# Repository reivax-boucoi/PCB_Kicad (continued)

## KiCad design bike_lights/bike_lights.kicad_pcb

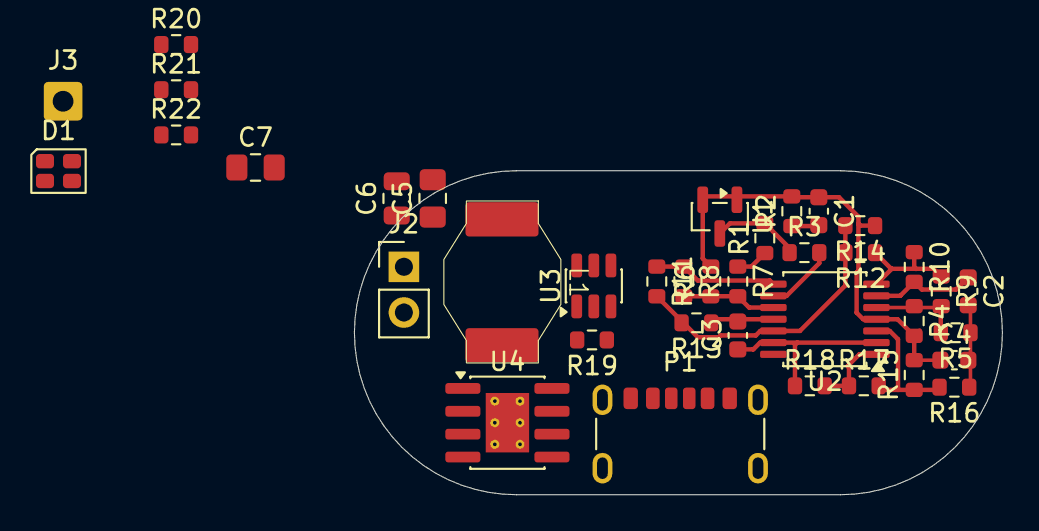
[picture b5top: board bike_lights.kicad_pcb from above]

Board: 2 copper layers, 36.0 x 18.0 mm, 39 parts (1 on the bottom side), 23 nets.

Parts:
C1, C3, C4: 100n; C_0603_1608Metric
C2: 470n; C_0603_1608Metric
C5, C7: 10u; C_0805_2012Metric_Pad1.18x1.45mm_HandSolder
C6: 270n; C_0805_2012Metric
D1: LED_Dual_AAKK; LED_Cree-PLCC4_2x2mm_CW
H1: MountingHole_Pad; SolderWirePad_1x01_SMD_5x10mm
J2: LED; PinHeader_1x02_P2.54mm_Vertical
J3: B+; SolderWire-0.5sqmm_1x01_D0.9mm_OD2.1mm
L1: 10µ; DO1813H
P1: USB_C_Plug_USB2.0; USB_C_Receptacle_GCT_USB4125-xx-x_6P_TopMnt_Horizontal
R1, R20, R21, R22: 1k96; R_0603_1608Metric
R2: 51k; R_0603_1608Metric
R3, R13, R18: 33k; R_0603_1608Metric
R4, R5, R6, R7, R9, R14, R15, R16, R17: 39k; R_0603_1608Metric
R8: 1M; R_0603_1608Metric
R10: 680k; R_0603_1608Metric
R11: 100k; R_0603_1608Metric
R12: 56k; R_0603_1608Metric
R19: 2R2; R_0603_1608Metric
U1: TL431DBZ; SOT-23
U2: MCP6004; TSSOP-14_4.4x5mm_P0.65mm
U3: MIC2289; SOT-23-6
U4: TP4056-42-ESOP8; SOIC-8-1EP_3.9x4.9mm_P1.27mm_EP2.41x3.3mm_ThermalVias

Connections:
+BATT: C1.1, C4.1, C5.1, J3.1, L1.1, R2.2, R4.2, R6.2, R14.1, R15.2, U1.1 (K), U1.2 (REF), U2.4 (V+), U3.5 (Vin), U4.5 (BAT)
/Batt_mon: R6.1, R7.2, R8.2, U2.10 (+)
/Blink: R9.1, R10.1, R12.1, U2.7
/BlinkFB: R4.1, R5.2, R9.2, U2.5 (+)
/BlinkRC: C2.1, R10.2, U2.6 (-)
/EN: U2.14, U3.4 (EN)
/LED+: C6.1, J2.1, U3.6 (OUT)
/LED-: J2.2, R19.1, U3.3 (FB)
/LowBat: R8.1, R11.1, U2.8
/Ramp: C3.1, R18.1, U2.2 (-), U2.13 (-)
/RampFB: R15.1, R16.2, R17.2, U2.3 (+)
/RampOut: R17.1, R18.2, U2.1
/SW: L1.2, U3.1 (SW)
/Sum: R11.2, R12.2, R13.2, R14.2, U2.12 (+)
/Vref: C1.2, R2.1, R3.2, U2.9 (-)
/~CHRG: D1.4 (K2), R20.1
/~STDBY: D1.3 (K1), R21.1
GND: C2.2, C3.2, C4.2, C5.2, C6.2, C7.2, H1.1, P1.A12 (GND), P1.B12 (GND), P1.S1 (SHIELD), R1.1, R5.1, R7.1, R13.1, R16.1, R19.2, R22.1, U2.11 (V-), U3.2 (GND), U4.3 (GND), U4.9 (EPAD)
unnamed: C7.1, D1.1 (A1), D1.2 (A2), P1.A9 (VBUS), P1.B9 (VBUS), U4.4 (V_{CC}), U4.8 (CE)
unnamed: R1.2, R3.1, U1.3 (A)
unnamed: R22.2, U4.2 (PROG)
unnamed: R20.2, U4.7 (~CHRG)
unnamed: R21.2, U4.6 (~STDBY)

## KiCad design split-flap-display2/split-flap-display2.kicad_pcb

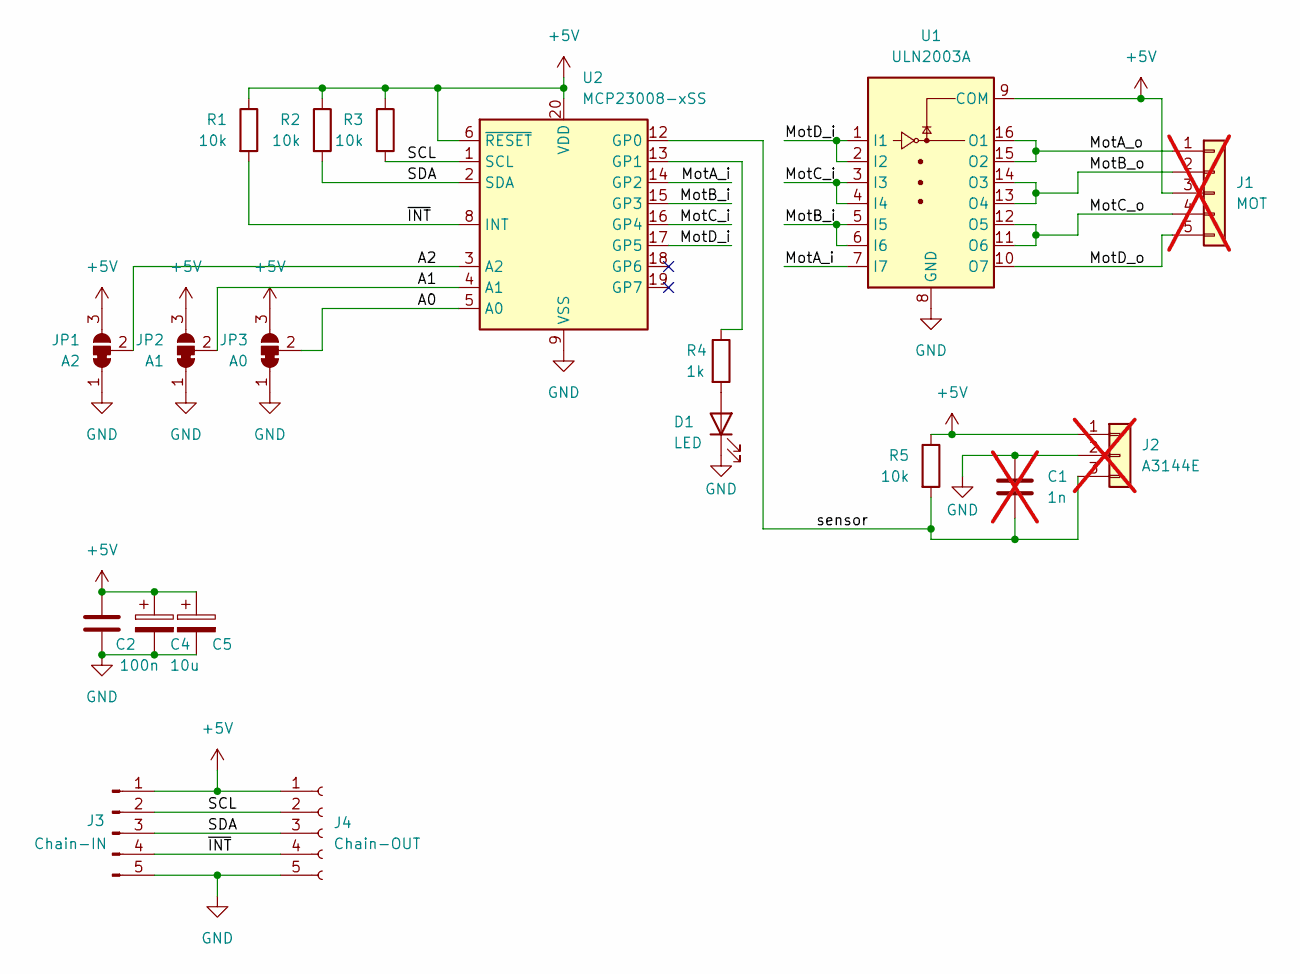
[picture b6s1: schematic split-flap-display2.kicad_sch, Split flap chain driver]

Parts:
C1: 1n; C_0402_1005Metric_Pad0.74x0.62mm_HandSolder; not fitted
C2: 100n; C_0603_1608Metric_Pad1.08x0.95mm_HandSolder
C4, C5: 10u; C_0805_2012Metric_Pad1.18x1.45mm_HandSolder
D1: LED; LED_0603_1608Metric_Pad1.05x0.95mm_HandSolder
J1: MOT; PinHeader_1x05_P2.54mm_Vertical; not fitted
J2: A3144E; PinHeader_1x03_P2.54mm_Vertical; not fitted
J3: Chain-IN; PinHeader_1x05_P2.54mm_Horizontal
J4: Chain-OUT; PinSocket_1x05_P2.54mm_Horizontal
JP1: A2; SolderJumper-3_P1.3mm_Bridged12_RoundedPad1.0x1.5mm
JP2: A1; SolderJumper-3_P1.3mm_Bridged12_RoundedPad1.0x1.5mm
JP3: A0; SolderJumper-3_P1.3mm_Bridged12_RoundedPad1.0x1.5mm
R1, R2, R3, R5: 10k; R_0603_1608Metric_Pad0.98x0.95mm_HandSolder
R4: 1k; R_0603_1608Metric_Pad0.98x0.95mm_HandSolder
U1: ULN2003A; SOIC-16_3.9x9.9mm_P1.27mm
U2: MCP23008-xSS; SSOP-20_5.3x7.2mm_P0.65mm

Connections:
+5V: C2.1, C4.1, C5.1, J1.3, J2.1, J3.1, J4.1, JP1.3 (B), JP2.3 (B), JP3.3 (B), R1.1, R2.1, R3.1, R5.1, U1.9 (COM), U2.6 (~RESET), U2.20 (VDD)
/A0: JP3.2 (C), U2.5 (A0)
/A1: JP2.2 (C), U2.4 (A1)
/A2: JP1.2 (C), U2.3 (A2)
/MotA_i: U1.7 (I7), U2.14 (GP2)
/MotA_o: J1.1, U1.15 (O2), U1.16 (O1)
/MotB_i: U1.5 (I5), U1.6 (I6), U2.15 (GP3)
/MotB_o: J1.2, U1.13 (O4), U1.14 (O3)
/MotC_i: U1.3 (I3), U1.4 (I4), U2.16 (GP4)
/MotC_o: J1.4, U1.11 (O6), U1.12 (O5)
/MotD_i: U1.1 (I1), U1.2 (I2), U2.17 (GP5)
/MotD_o: J1.5, U1.10 (O7)
/SCL: J3.2, J4.2, R3.2, U2.1 (SCL)
/SDA: J3.3, J4.3, R2.2, U2.2 (SDA)
/sensor: C1.2, J2.3, R5.2, U2.12 (GP0)
/~INT: J3.4, J4.4, R1.2, U2.8 (INT)
GND: C1.1, C2.2, C4.2, C5.2, D1.1 (K), J2.2, J3.5, J4.5, JP1.1 (A), JP2.1 (A), JP3.1 (A), U1.8 (GND), U2.9 (VSS)
unnamed: D1.2 (A), R4.2
unnamed: R4.1, U2.13 (GP1)

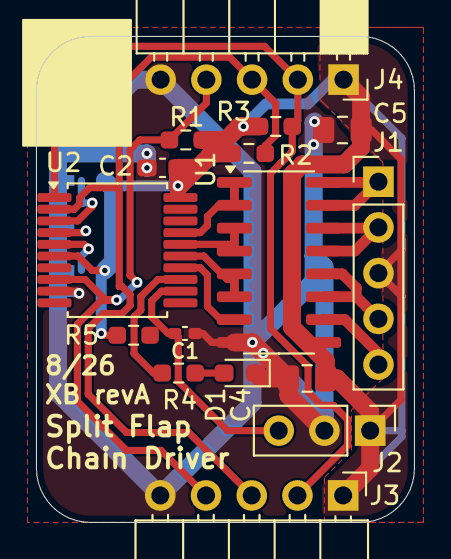
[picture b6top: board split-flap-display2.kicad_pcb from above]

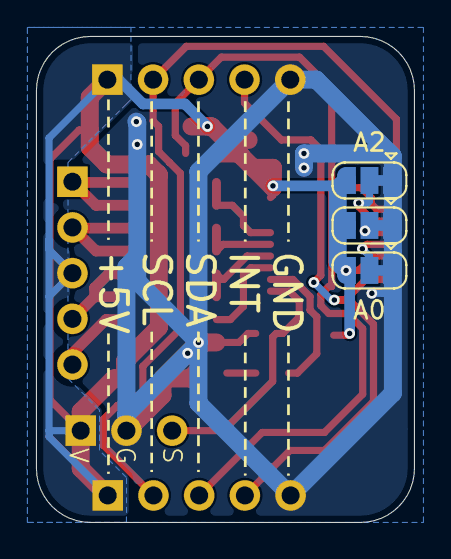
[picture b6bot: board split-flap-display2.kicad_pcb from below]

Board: 2 copper layers, 21.0 x 27.0 mm, 19 parts (3 on the bottom side), 19 nets.

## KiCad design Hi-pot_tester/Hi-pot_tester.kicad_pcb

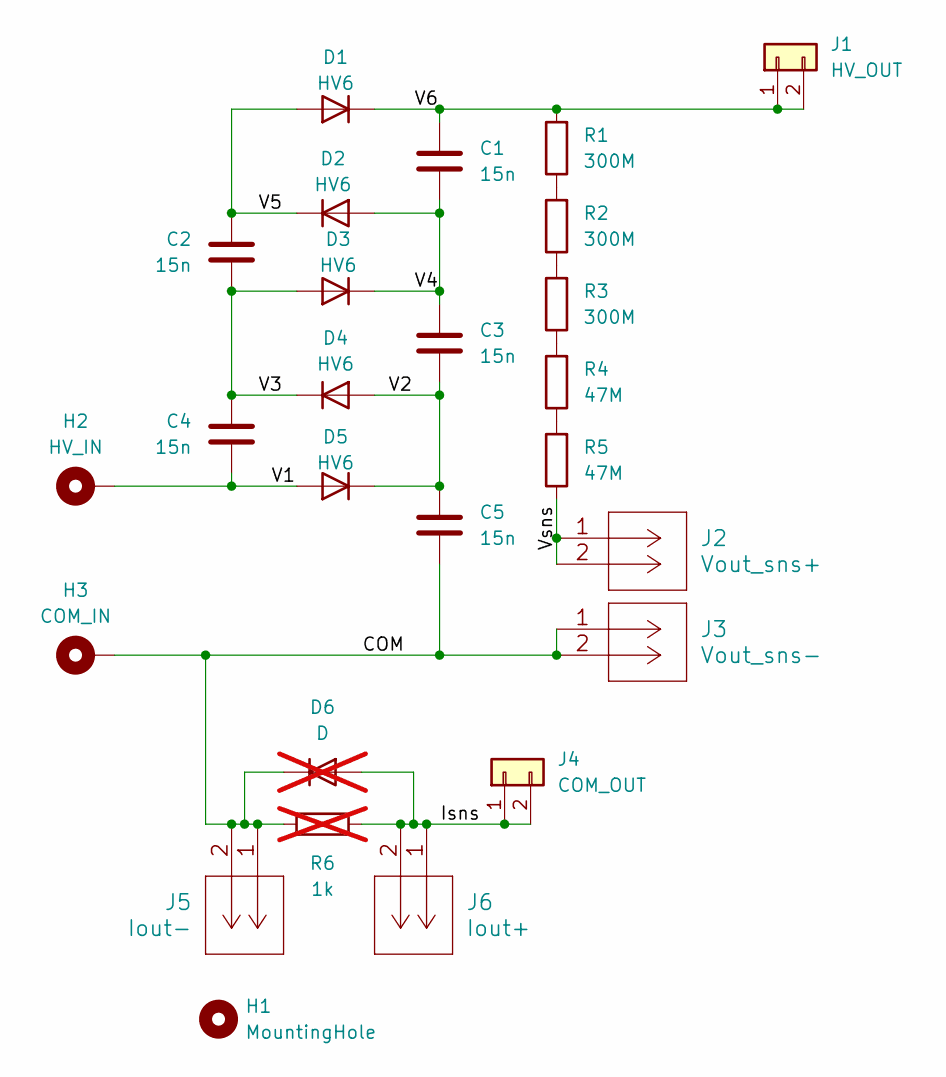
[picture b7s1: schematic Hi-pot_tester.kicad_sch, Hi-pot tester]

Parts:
C1, C2, C3, C4, C5: 15n; C_Rect_L41.5mm_W13.0mm_P37.50mm_MKS4
D1, D2, D3, D4, D5: HV6; D_DO-15_P15.24mm_Horizontal
D6: D; D_A-405_P7.62mm_Horizontal; not fitted
H1: MountingHole; MountingHole_4.3mm_M4
H2: HV_IN; MountingHole_3.2mm_M3_Pad_Via
H3: COM_IN; MountingHole_3.2mm_M3_Pad_Via
J1: HV_OUT; PinHeader_1x02_P2.54mm_Vertical
J2: Vout_sns+; 105-1102-001
J3: Vout_sns-; 105-1102-001
J4: COM_OUT; PinHeader_1x02_P2.54mm_Vertical
J5: Iout-; 105-1102-001
J6: Iout+; 105-1102-001
R1, R2, R3: 300M; HB01RE
R4, R5: 47M; R_Axial_DIN0309_L9.0mm_D3.2mm_P12.70mm_Horizontal
R6: 1k; R_Axial_DIN0309_L9.0mm_D3.2mm_P12.70mm_Horizontal; not fitted

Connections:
/COM: C5.2, D6.1 (K), H3.1, J3.1, J3.2, J5.1, J5.2, R6.1
/Isns: D6.2 (A), J4.1, J4.2, J6.1, J6.2, R6.2
/V1: C4.2, D5.2 (A), H2.1
/V2: C3.2, C5.1, D4.2 (A), D5.1 (K)
/V3: C2.2, C4.1, D3.2 (A), D4.1 (K)
/V4: C1.2, C3.1, D2.2 (A), D3.1 (K)
/V5: C2.1, D1.2 (A), D2.1 (K)
/V6: C1.1, D1.1 (K), J1.1, J1.2, R1.2
/Vsns: J2.1, J2.2, R5.1
unnamed: R1.1, R2.2
unnamed: R2.1, R3.2
unnamed: R3.1, R4.2
unnamed: R4.1, R5.2

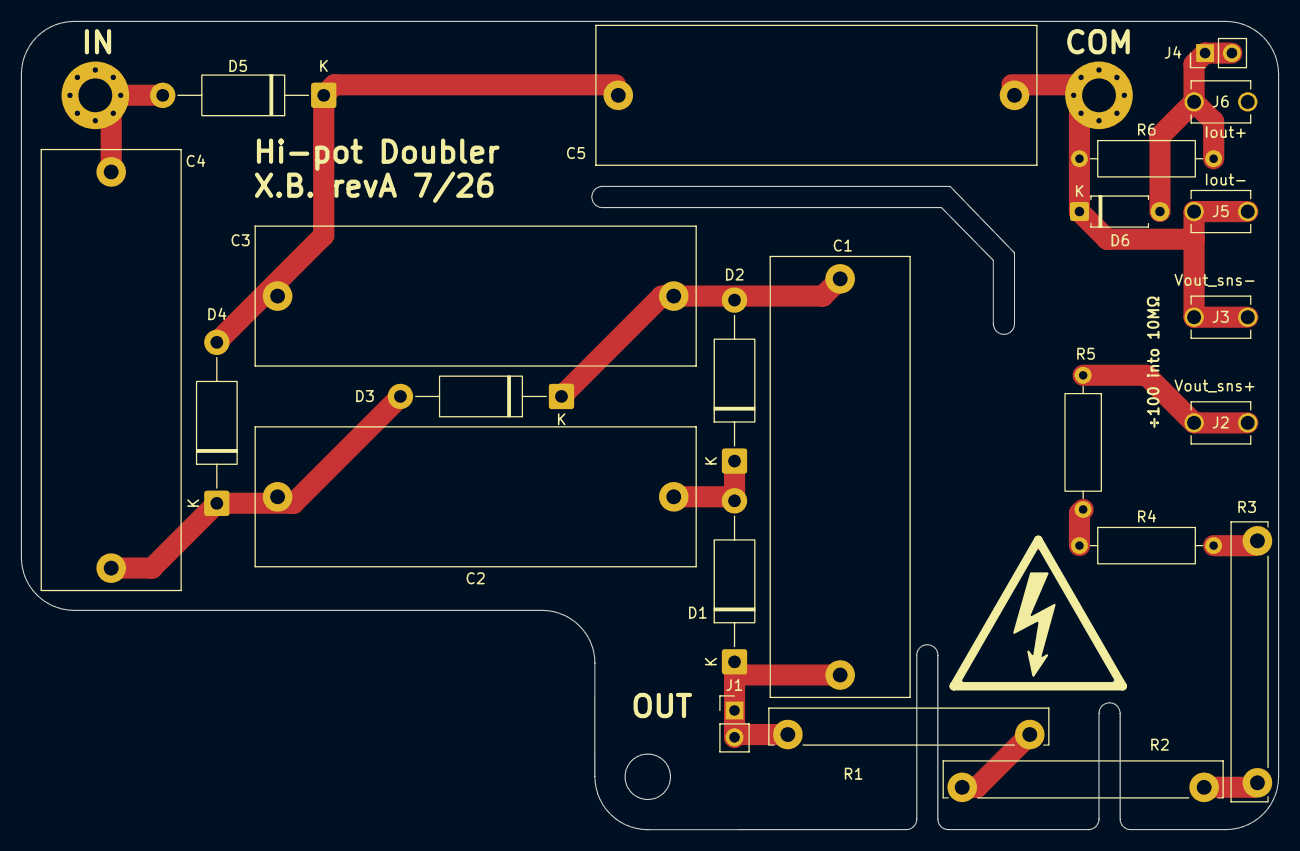
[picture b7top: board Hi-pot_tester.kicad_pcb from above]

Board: 2 copper layers, 119.0 x 76.5 mm, 26 parts (0 on the bottom side), 13 nets.

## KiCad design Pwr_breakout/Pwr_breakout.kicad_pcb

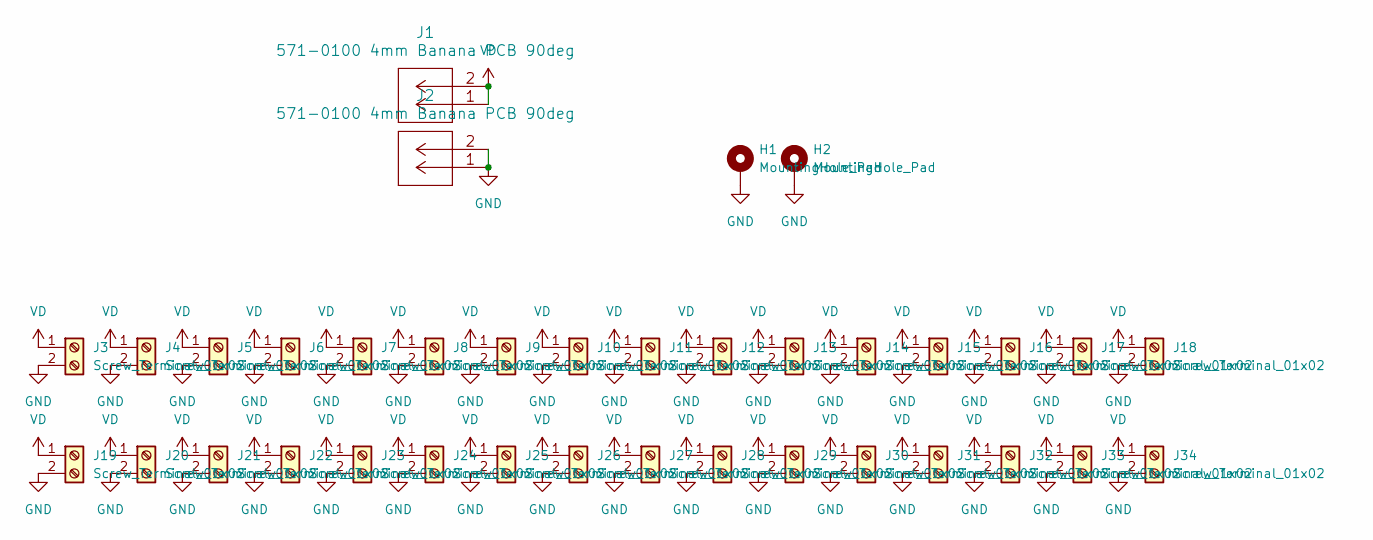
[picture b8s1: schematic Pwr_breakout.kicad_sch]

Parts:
H1, H2: MountingHole_Pad; MountingHole_6.4mm_M6_Pad_Via
J1, J2: 571-0100 4mm Banana PCB 90deg; 571-0100_Black
J3, J4, J5, J6, J7, J8, J9, J10, J11, J12, J13, J14, J15, J16, J17, J18, J19, J20, J21, J22, J23, J24, J25, J26, J27, J28, J29, J30, J31, J32, J33, J34: Screw_Terminal_01x02; TerminalBlock_bornier-2_P5.08mm

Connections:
GND: H1.1, H2.1, J2.1, J2.2, J3.2, J4.2, J5.2, J6.2, J7.2, J8.2, J9.2, J10.2, J11.2, J12.2, J13.2, J14.2, J15.2, J16.2, J17.2, J18.2, J19.2, J20.2, J21.2, J22.2, J23.2, J24.2, J25.2, J26.2, J27.2, J28.2, J29.2, J30.2, J31.2, J32.2, J33.2, J34.2
VD: J1.1, J1.2, J3.1, J4.1, J5.1, J6.1, J7.1, J8.1, J9.1, J10.1, J11.1, J12.1, J13.1, J14.1, J15.1, J16.1, J17.1, J18.1, J19.1, J20.1, J21.1, J22.1, J23.1, J24.1, J25.1, J26.1, J27.1, J28.1, J29.1, J30.1, J31.1, J32.1, J33.1, J34.1

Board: 2 copper layers, 36 parts (0 on the bottom side), 2 nets, no tracks yet.

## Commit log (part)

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2022-01-01 added project
2022-01-02 first commit"
2022-01-03 added gitignore
2022-01-09 added case
2023-04-11 initial sw
2023-04-11 PCINT and LCD low power
2023-04-12 reorg wieght scale folder
2023-04-13 weight scale SW progress
2023-04-16 uart under test
2023-04-23 ADC basics
2023-05-24 Slide switch library
2023-08-25 library added mini360
2023-08-26 library added bluesmirf
2023-08-26 library mini360
2023-08-26 added board gerbers
2023-08-26 updated gitignore
2023-08-30 removed backups
2023-08-30 added usb mini through hole
2023-08-30 added sch pdfs
2023-08-30 removed old .pro
2023-09-01 added hall sensor
2023-09-19 added HBI & XM3 steps
2023-09-20 added v2
2023-09-24 added led driver calcs
2023-09-26 created MIC28517
2023-09-26 added pending items
2023-09-27 added ltspice
2023-09-27 seconds_minor_wrapup
2023-09-27 seconds_major_wrapup
2023-09-28 added content
2023-11-01 found sch issue
2024-01-09 added svg viz
2025-03-31 ajout vues 3D
2025-11-05 added base SW
2025-11-05 added ESP library
2025-11-05 added preliminary sch
2025-11-06 added .lck
2025-11-18 added proto v0
2025-11-18 added TODO list
2025-11-18 added schematic pdf export
2025-11-28 fix typo
2026-02-17 added slider 3D model
2026-02-24 added mot pot lib
2026-03-04 local nx comm
2026-03-25 added PCB_Ventil revA
2026-03-25 new rev with Mano
2026-03-25 new BOM with resistors
2026-04-08 added .zip
